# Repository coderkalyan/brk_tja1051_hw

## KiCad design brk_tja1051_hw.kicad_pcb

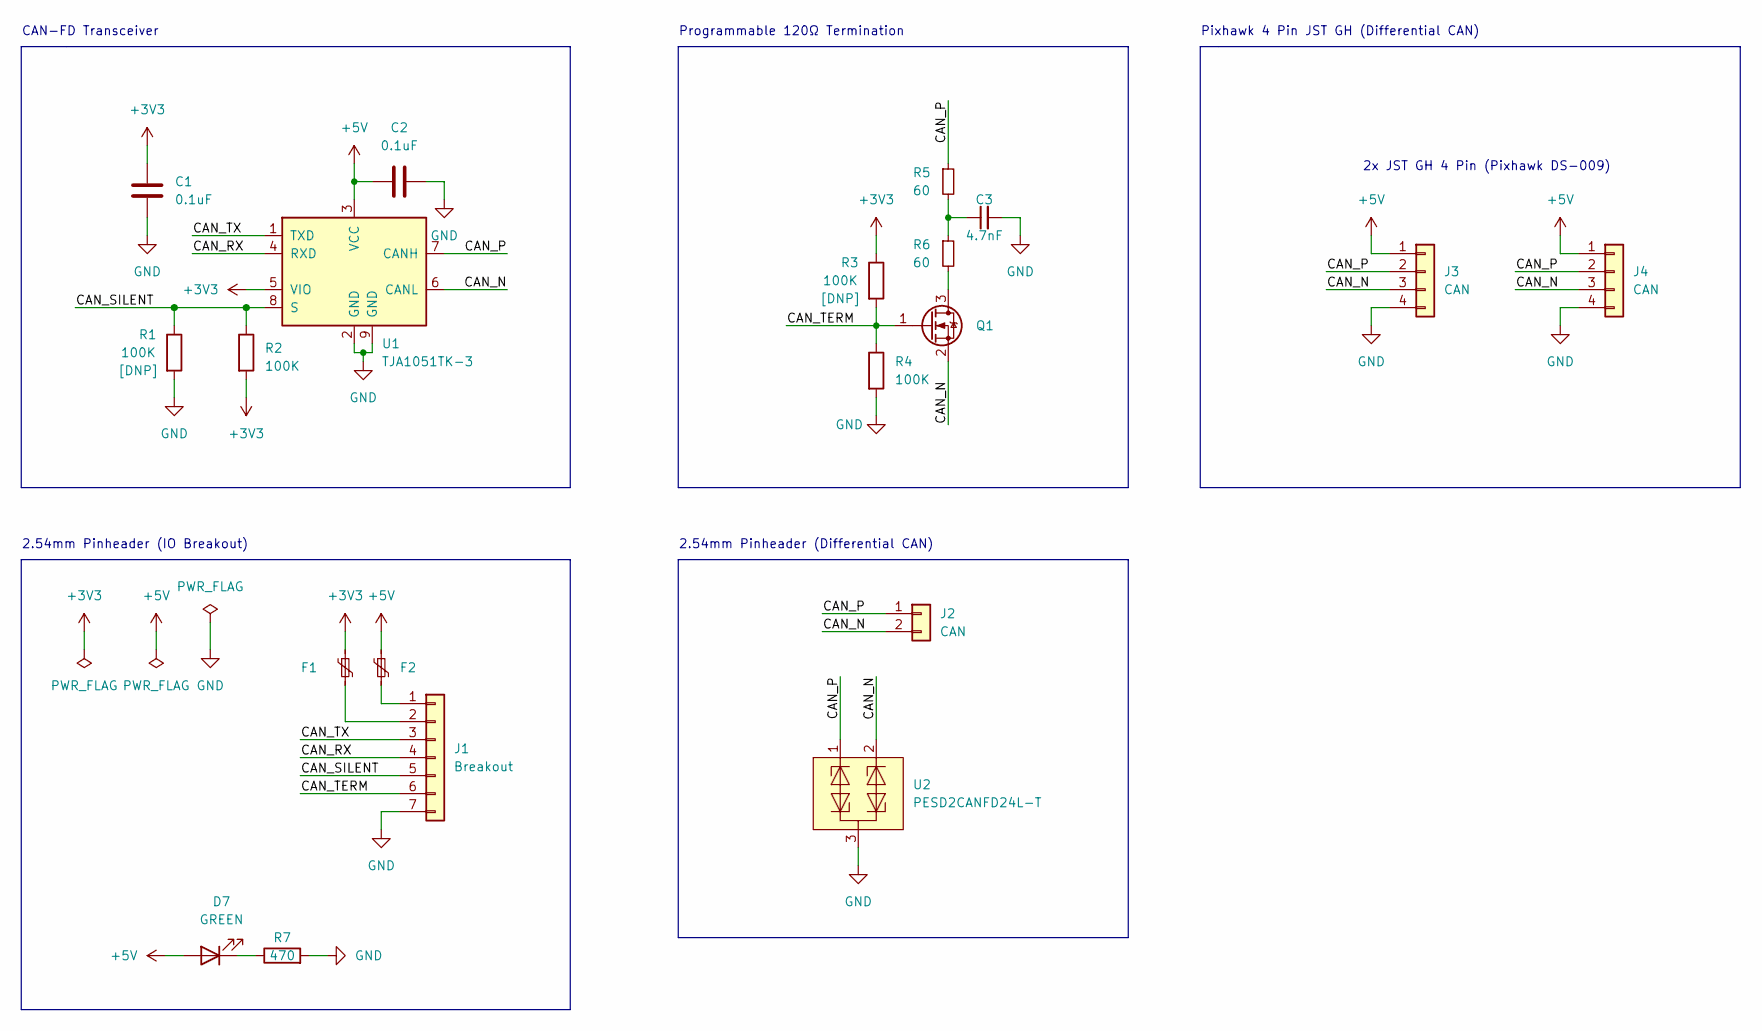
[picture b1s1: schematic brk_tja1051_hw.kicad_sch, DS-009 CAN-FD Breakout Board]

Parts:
C1, C2: 0.1uF; C_0402_1005Metric; LCSC C1525
C3: 4.7nF; C_0402_1005Metric; LCSC C1538
D7: GREEN; LED_0603_1608Metric; LCSC C72043
F1, F2: Polyfuse_Small; Fuse_0805_2012Metric; LCSC C341812
J1: Breakout; PinHeader_1x07_P2.54mm_Vertical
J2: CAN; PinHeader_1x02_P2.54mm_Vertical
J3, J4: CAN; JST_GH_SM04B-GHS-TB_1x04-1MP_P1.25mm_Horizontal; LCSC C189895
Q1: Q_NMOS_GSD; SOT-23; LCSC C8545
R1, R2, R3, R4: 100K; R_0402_1005Metric; LCSC C25741
R5, R6: 60; R_0402_1005Metric; LCSC C2960873
R7: 470; R_0402_1005Metric; LCSC C25117
U1: TJA1051TK-3; DFN-8-1EP_3x3mm_P0.65mm_EP1.55x2.4mm; LCSC C124020
U2: PESD2CANFD24L-T; SOT-23; LCSC C2687131

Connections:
+3V3: C1.1, F1.1, R2.2, R3.1, U1.5 (VIO)
+5V: C2.1, D7.2 (A), F2.1, J3.1, J4.1, U1.3 (VCC)
/CAN_N: J2.2, J3.3, J4.3, Q1.2 (S), U1.6 (CANL), U2.2
/CAN_P: J2.1, J3.2, J4.2, R5.1, U1.7 (CANH), U2.1
/CAN_RX: J1.4, U1.4 (RXD)
/CAN_SILENT: J1.5, R1.1, R2.1, U1.8 (S)
/CAN_TERM: J1.6, Q1.1 (G), R3.2, R4.1
/CAN_TX: J1.3, U1.1 (TXD)
GND: C1.2, C2.2, C3.2, J1.7, J3.4, J4.4, R1.2, R4.2, R7.2, U1.2 (GND), U1.9 (GND), U2.3
unnamed: C3.1, R5.2, R6.1
unnamed: D7.1 (K), R7.1
unnamed: F1.2, J1.2
unnamed: F2.2, J1.1
unnamed: Q1.3 (D), R6.2

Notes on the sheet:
2.54mm Pinheader (Differential CAN)
Pixhawk 4 Pin JST GH (Differential CAN)
Programmable 120Ω Termination
2x JST GH 4 Pin (Pixhawk DS-009)
CAN-FD Transceiver
2.54mm Pinheader (IO Breakout)

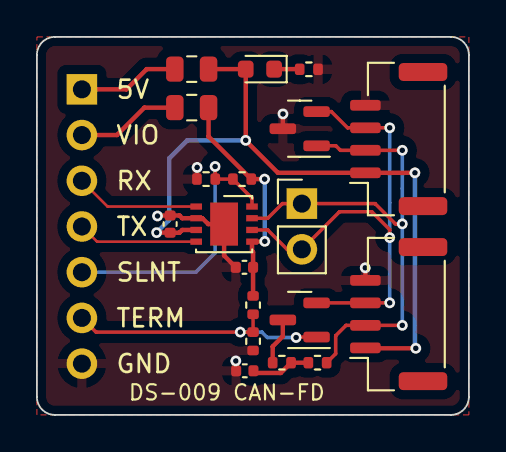
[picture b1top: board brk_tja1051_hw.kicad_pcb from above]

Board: 2 copper layers, 24.0 x 21.0 mm, 20 parts (1 on the bottom side), 14 nets.
